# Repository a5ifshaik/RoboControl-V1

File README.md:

# RoboControl V1 - Arduino-based Robot Control Board
<p align="justify"> The RoboControl is a cheap and beginner-friendly all-in-one robot control board which is capable of dual motor control (6A/Channel), and includes dedicated pinouts for servos, sensors and external 12V systems which is controlled using a MOSFET. It also features a built in battery level sensing circuit which is made up of a simple voltage divider that translates the 0-12V range of the input battery to a analog value range between 0-1023. </p>

## Features
- 12V - 24V Input Voltage
- Arduino Nano MCU
- Two Infineon IFX9201SG Motor Drivers (Supports up to 6A/driver)
- MOSFET for External Circuit Control
- Battery Voltage Monitor
- Dedicated ports for sensors/servos

## Pinout 
| On RCB        | Arduino Pin   |                             Description                        | 
| ------------- | ------------- |  ------------------------------------------------------------- |
| S1            | D6            | Servo 1 Port; comes with 5V and GND supply                     |
| S2            | D9            | Servo 2 Port; comes with 5V and GND supply                     |
| SCL           | A5            | Serial Clock Line used for I2C                                 | 
| SDA           | A4            | Serial Data Line used for I2C                                  | 
| BZOUT         | D7            | MOSFET control line, 5V to turn on 12V line                    |
| TRIG          | D12           | Trigger Pin for Ultrasonic Sensor (Can use as normal digital)  |
| ECHO          | D11           | Echo Pin for Ultrasonic Sensor (Can use as normal digital)     |
| BATT          | A3            | Battery monitor pin, produces analog reading between 0 - 1023  |
| M1 PWM        | D3            | PWM Signal supply pin for Motor 1 driver                       |
| M1 DIR        | D8            | Motor 1 Direction Pin (1/0 for CW/CCW or vv)                   |
| M1 EN         | D2            | Motor 1 Enable Pin, Set as HIGH to enable driver               |
| M2 PWM        | D5            | PWM Signal supply pin for Motor 2 driver                       |
| M2 DIR        | D10           | Motor 2 Direction Pin (1/0 for CW/CCW or vv)                   |
| M2 EN         | D4            | Motor 2 Enable Pin, Set as HIGH to enable driver               |

## Schematics:

## 3D Render

## Sample Applications
### The RoboControl board was initially developed for a home-surveillance robot with 2 wheels, but can be used for various applications that have similar needs.

###### **In Image 2, the yellow jumpers are used to correct an error found post-production which has since been rectified in this repository.

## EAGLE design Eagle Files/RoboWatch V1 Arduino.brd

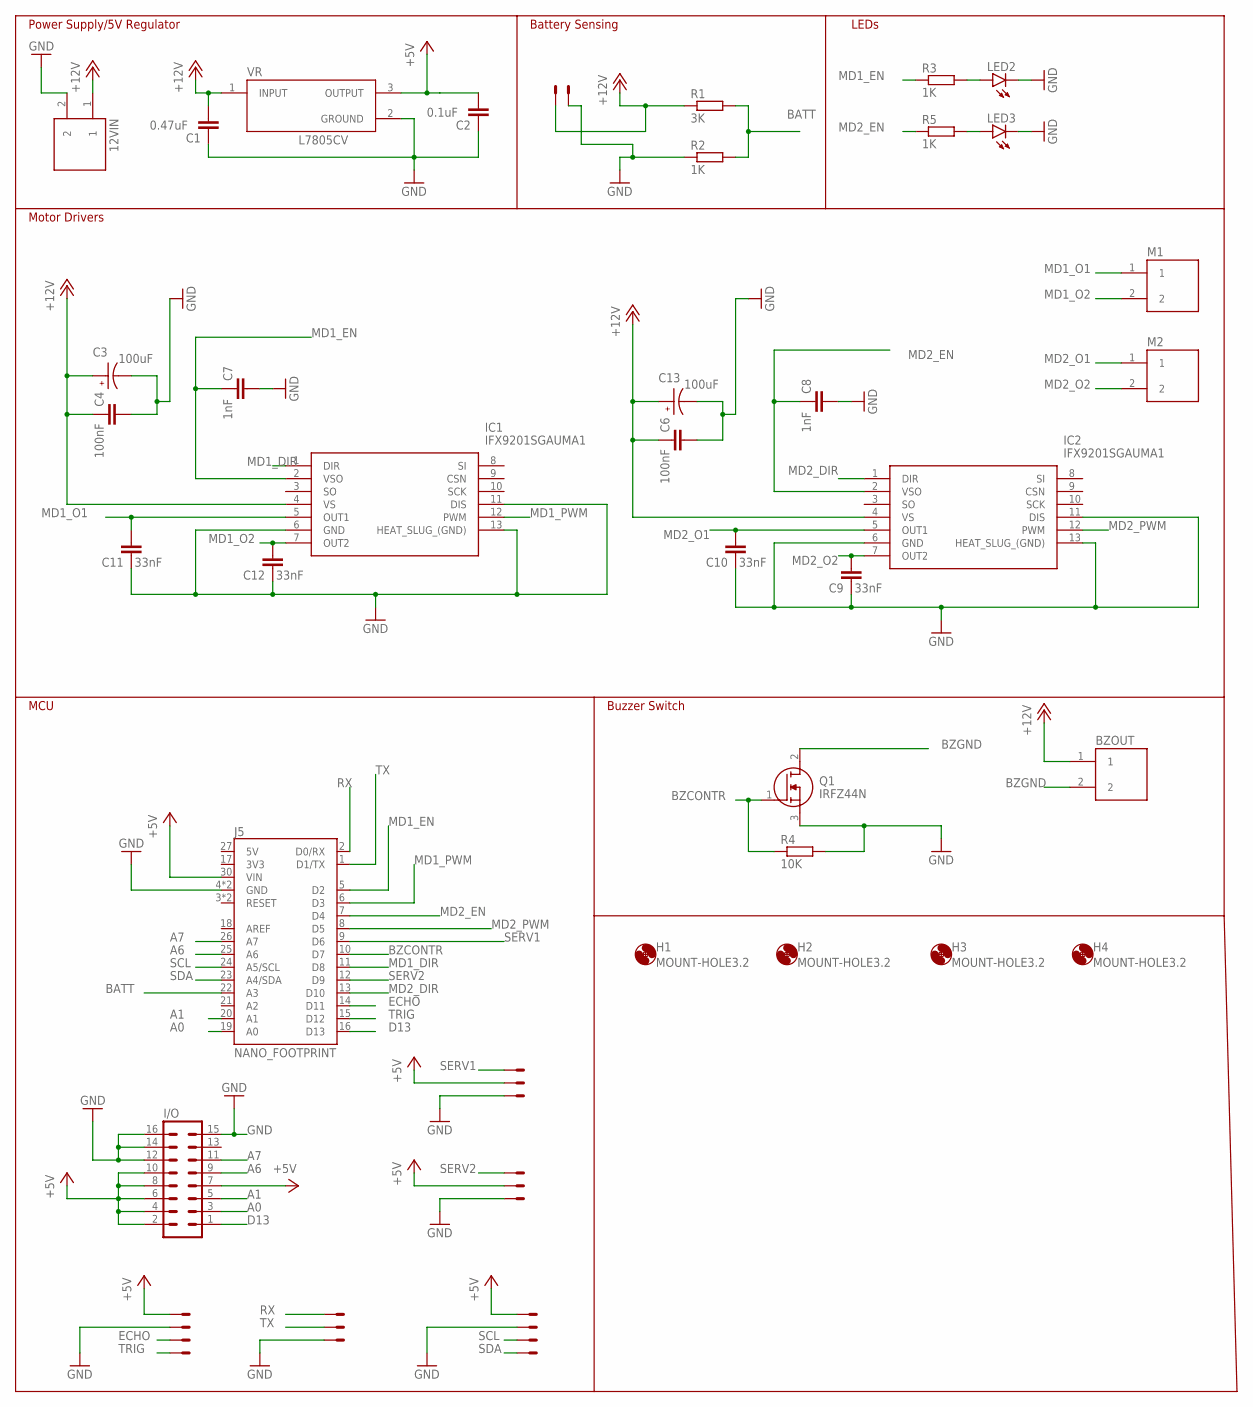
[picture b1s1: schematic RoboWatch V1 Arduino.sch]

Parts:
12VIN: KF301-2P; HANDSON_KF301-2P
BZOUT: KF301-2P; HANDSON_KF301-2P
C1: 0.47uF; C0603
C2: 0.1uF; C0603
C3, C13: 100uF; CAP_EEEFN1E101UP
C4, C6: 100nF; C0603
C7, C8: 1nF; C0603
C9, C10, C11, C12: 33nF; C0603
H1, H2, H3, H4: MOUNT-HOLE3.2; 3,2
I2C: 22-23-2041
I/O: MA08-2
IC1, IC2: IFX9201SGAUMA1; PG-DSO-12-17
J5: NANO_FOOTPRINT; NANO
LED2, LED3: LEDCHIPLED_0805; CHIPLED_0805
M1, M2: KF301-2P; HANDSON_KF301-2P
Q1: IRFZ44N; TO254P440X1000X1900-3P
R1: 3K; R0603
R2, R3, R5: 1K; R0603
R4: 10K; R0603
RX/TX: 22-23-2031
S1, S2: 22-23-2031
US: 22-23-2041
VR: L7805CV; TO255P1040X460X1968-3
X4: 22-23-2021

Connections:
+5V: C2.2, I2C.1, I/O.2, I/O.4, I/O.6, I/O.7, I/O.8, I/O.10, J5.30 (VIN), S1.2, S2.2, US.1, VR.3 (OUTPUT)
+12V: 12VIN.1, BZOUT.1, C1.2, C3.1, C4.1, C6.1, C13.1, IC1.4 (VS), IC2.4 (VS), R1.1, VR.1 (INPUT), X4.1
A0: I/O.3, J5.19 (A0)
A1: I/O.5, J5.20 (A1)
A6: I/O.9, J5.25 (A6)
A7: I/O.11, J5.26 (A7)
BATT: J5.22 (A3), R1.2, R2.2
BZCONTR: J5.10 (D7), Q1.1 (G), R4.1
BZGND: BZOUT.2, Q1.2 (D)
D13: I/O.1, J5.16 (D13)
ECHO: J5.14 (D11), US.3
GND: 12VIN.2, C1.1, C2.1, C3.2, C4.2, C6.2, C7.2, C8.2, C9.1, C10.1, C11.1, C12.1, C13.2, I2C.2, I/O.12, I/O.14, I/O.15, I/O.16, IC1.6 (GND), IC1.11 (DIS), IC1.13 (HEAT_SLUG_(GND)), IC2.6 (GND), IC2.11 (DIS), IC2.13 (HEAT_SLUG_(GND)), J5.4 (GND), J5.29 (GND), LED2.C, LED3.C, Q1.3 (S), R2.1, R4.2, RX/TX.3, S1.3, S2.3, US.2, VR.2 (GROUND), X4.2
MD1_DIR: IC1.1 (DIR), J5.11 (D8)
MD1_EN: C7.1, IC1.2 (VSO), J5.5 (D2), R3.1
MD1_O1: C11.2, IC1.5 (OUT1), M1.1
MD1_O2: C12.2, IC1.7 (OUT2), M1.2
MD1_PWM: IC1.12 (PWM), J5.6 (D3)
MD2_DIR: IC2.1 (DIR), J5.13 (D10)
MD2_EN: C8.1, IC2.2 (VSO), J5.7 (D4), R5.1
MD2_O1: C10.2, IC2.5 (OUT1), M2.1
MD2_O2: C9.2, IC2.7 (OUT2), M2.2
MD2_PWM: IC2.12 (PWM), J5.8 (D5)
unnamed: LED2.A, R3.2
unnamed: LED3.A, R5.2
RX: J5.2 (D0/RX), RX/TX.1
SCL: I2C.3, J5.24 (A5/SCL)
SDA: I2C.4, J5.23 (A4/SDA)
SERV1: J5.9 (D6), S1.1
SERV2: J5.12 (D9), S2.1
TRIG: J5.15 (D12), US.4
TX: J5.1 (D1/TX), RX/TX.2

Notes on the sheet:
Power Supply/5V Regulator
Motor Drivers
MCU
Battery Sensing
LEDs
Buzzer Switch

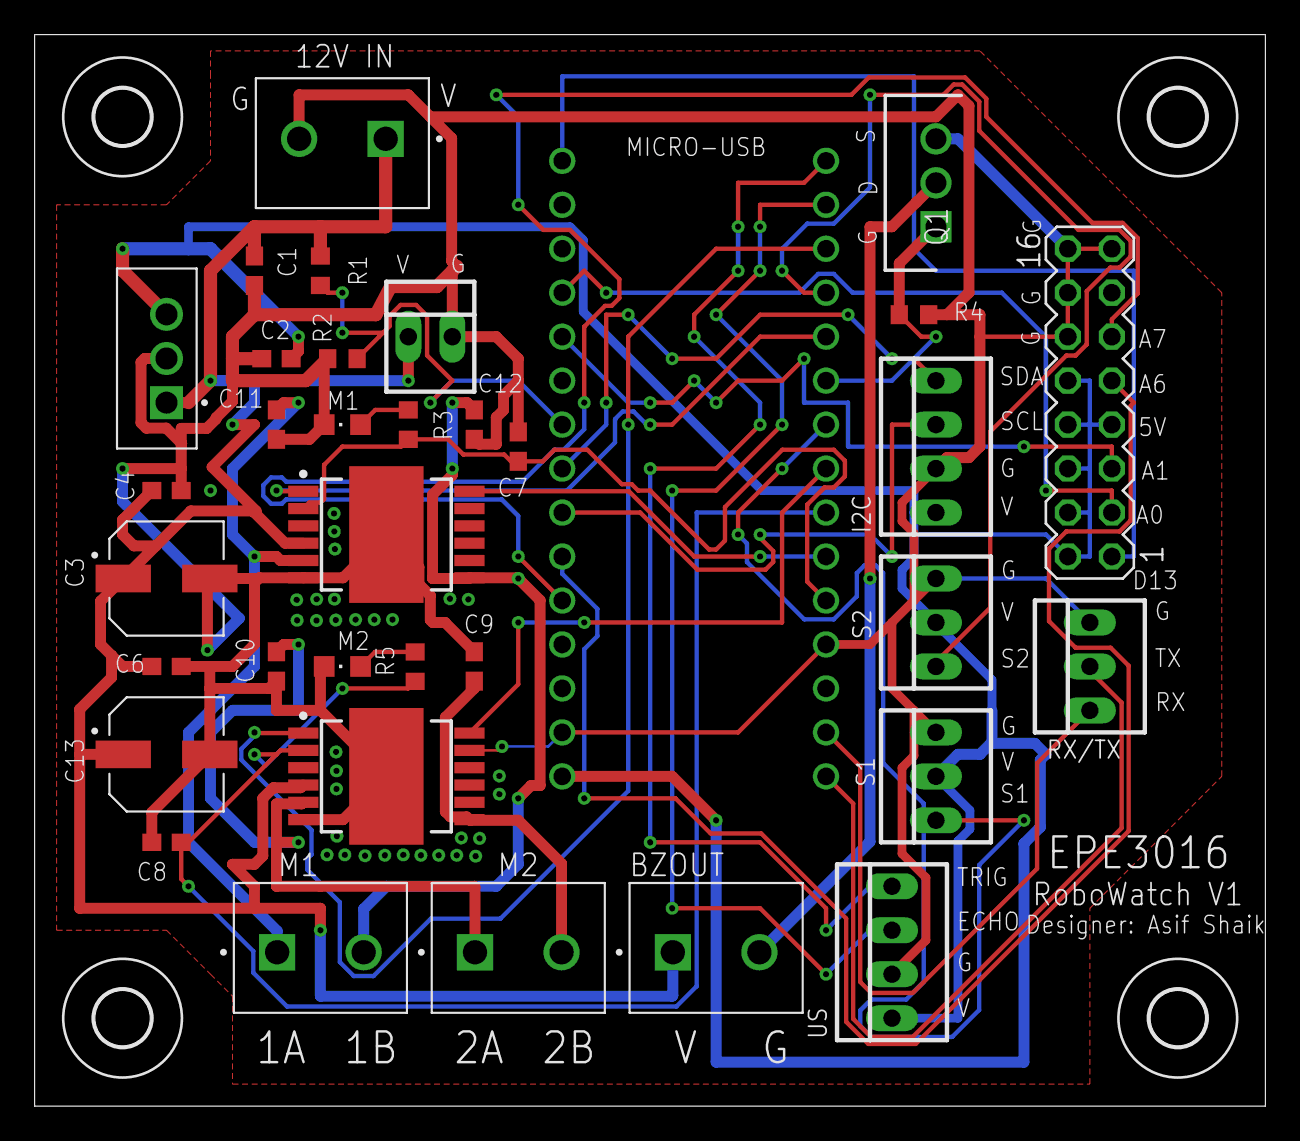
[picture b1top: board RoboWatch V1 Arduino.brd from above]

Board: 2 copper layers, 71.1 x 61.9 mm, 39 parts (0 on the bottom side), 31 nets.

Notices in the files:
parts and their libraries:
SparkFun-Boards: Licensing: Creative Commons ShareAlike 4.0 International - https://creativecommons.org/licenses/by-sa/4.0
